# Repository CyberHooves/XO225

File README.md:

Haos Redro PN 0000 0003
Stereo 2.5-way electronic crossover
===================================

This is a stereo two way electronic crossover with mono subwoofer output. All inputs and outputs are balanced.

This was designed with fixed crossover frequencies and fixed gains for fixed applications. Applications wherein an adjustible crossover would have it's knobs maladjusted by knobs resulting in awful sound and burnt voice coils.

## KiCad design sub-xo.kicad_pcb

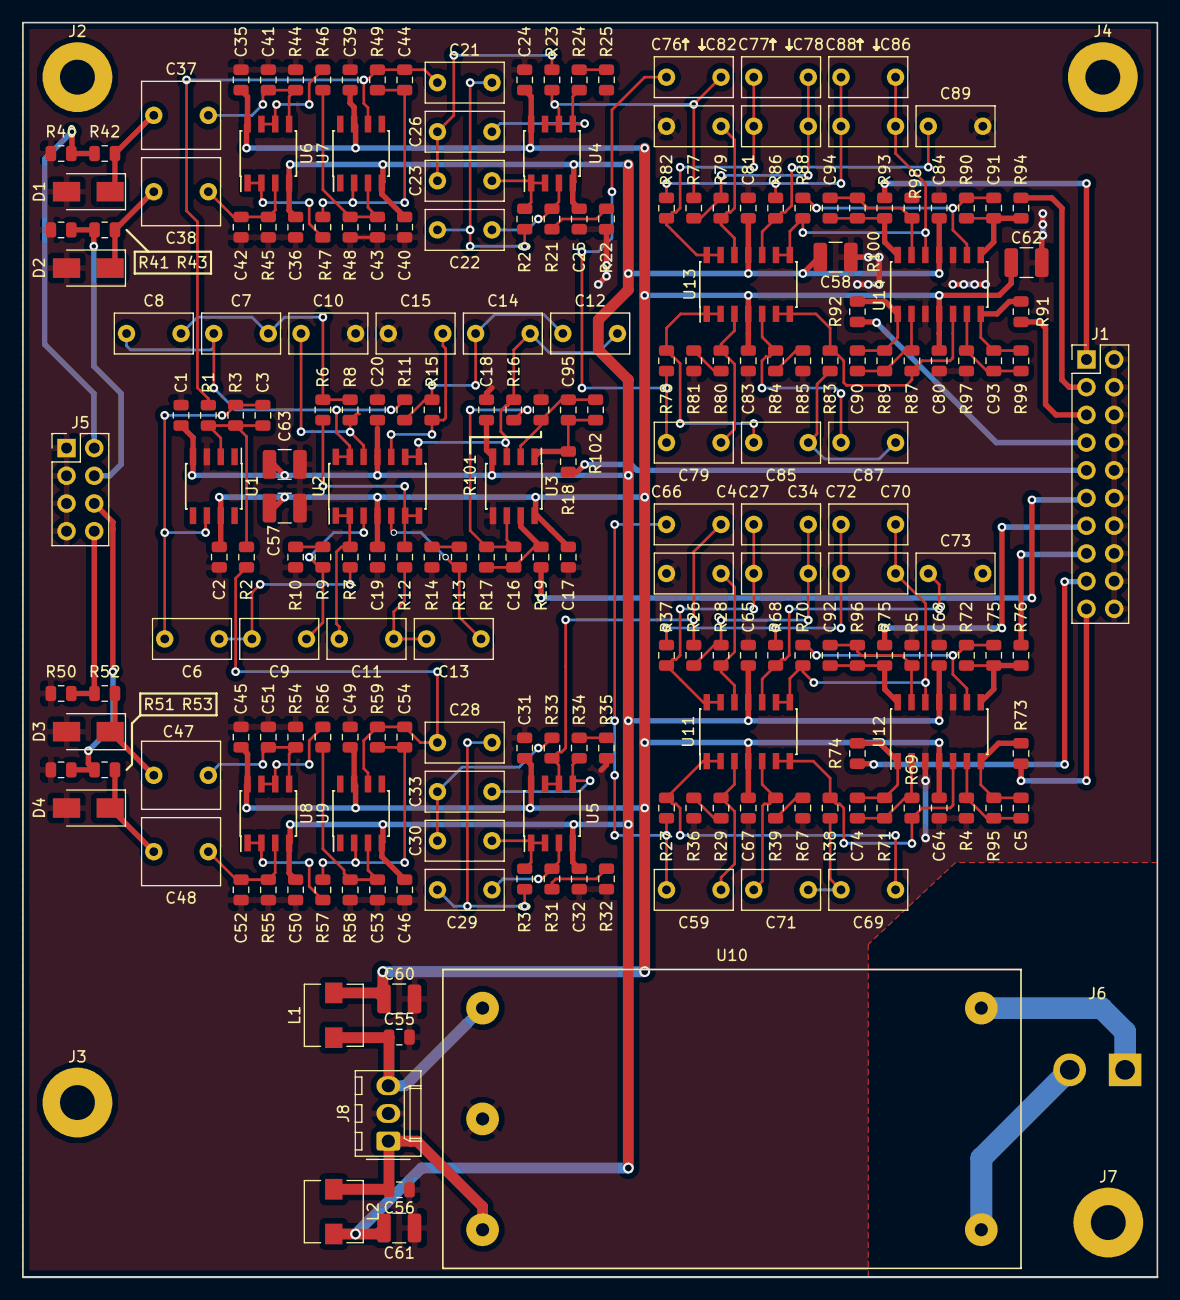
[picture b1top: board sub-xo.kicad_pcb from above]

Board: 2 copper layers, 104.0 x 115.0 mm, 218 parts (0 on the bottom side), 119 nets.

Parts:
C1, C2, C17, C18, C19, C20, C24, C25, C31, C32, C35, C36, C39, C40, C45, C46, C49, C50, C64, C65, C67, C68, C80, C81, C83, C84: 104; C_0805_2012Metric
C3, C5, C16, C43, C44, C53, C54, C74, C75, C90, C91, C92, C93, C94, C95: 151; C_0805_2012Metric
C4, C6, C9, C11, C13, C59, C69, C71, C76, C79, C85, C87: 334; C_Rect_L7.0mm_W3.5mm_P5.00mm
C7, C8, C10, C12, C14, C15, C21, C22, C23, C26, C27, C28, C29, C30, C33, C34, C66, C70, C72, C73, C77, C78, C82, C86, C88, C89: 224; C_Rect_L7.0mm_W3.5mm_P5.00mm
C37, C38, C47, C48: 105; C_Rect_L7.0mm_W6.0mm_P5.00mm
C41, C42, C51, C52: 101; C_0805_2012Metric
C55, C56: 105; C_0805_2012Metric
C57, C58, C60, C61, C62, C63: 335; C_1210_3225Metric
D1, D2, D3, D4: SMAJ7; D_SMA
J1: Conn_02x10_Odd_Even; PinHeader_2x10_P2.54mm_Vertical
J2, J3, J4, J7: Screwhole; MountingHole_3.2mm_M3_Pad
J5: Conn_02x04_Odd_Even; PinHeader_2x04_P2.54mm_Vertical
J6: Conn_01x02; CON-MOLEX-SPOX-5281-2P-V
J8: Conn_01x03; Molex_KK-254_AE-6410-03A_1x03_P2.54mm_Vertical
L1, L2: 22; L_Wuerth_HCI-5040
R1, R2, R3, R4, R5, R16, R42, R43, R46, R47, R48, R49, R52, R53, R56, R57, R58, R59, R69, R70, R72, R87, R88, R90, R97, R98, R101, R102: 10K; R_0805_2012Metric
R6, R8, R11, R15, R20, R21, R22, R23, R24, R25, R26, R28, R30, R31, R32, R33, R34, R35, R37, R68, R77, R79, R82, R86: 4K3; R_0805_2012Metric
R7, R9, R10, R12, R13, R14, R27, R29, R36, R38, R39, R67, R78, R80, R81, R83, R84, R85: 8K2; R_0805_2012Metric
R17, R71, R89, R95, R96, R99, R100: 20K; R_0805_2012Metric
R18, R19, R73, R74, R75, R76, R91, R92, R93, R94: 100; R_0805_2012Metric
R40, R41, R50, R51: 1M; R_0805_2012Metric
R44, R45, R54, R55: 220K; R_0805_2012Metric
U1, U7, U9: TL071; SOIC-8_3.9x4.9mm_P1.27mm
U2, U11, U12, U13, U14: TL074; SOIC-14_3.9x8.7mm_P1.27mm
U3, U4, U5, U6, U8: TL072; SOIC-8_3.9x4.9mm_P1.27mm
U10: RAC10-15DK277; RECOM-RAC10

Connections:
+15V: C2.2, C17.1, C19.1, C24.1, C31.1, C35.1, C39.1, C45.1, C49.1, C57.1, C60.1, C62.1, C64.1, C67.1, C80.1, C83.1, L1.2, U1.7, U2.4, U3.8, U4.8, U5.8, U6.8, U7.7, U8.8, U9.7, U11.4, U12.4, U13.4, U14.4
-15V: C1.1, C18.2, C20.2, C25.2, C32.2, C36.2, C40.2, C46.2, C50.2, C58.2, C61.2, C63.2, C65.2, C68.2, C81.2, C84.2, L2.2, U1.4, U2.11, U3.4, U4.4, U5.4, U6.4, U7.4, U8.4, U9.4, U11.11, U12.11, U13.11, U14.11
/CH1 XO/IN: C76.2, R23.1, R77.2, U4.6, U4.7
/CH1 highpass/IN: C21.2, C44.1, R1.2, R49.1, U7.6
/CH1_HI+: J1.5, R91.1
/CH1_HI-: J1.7, R92.1
/CH1_IN+: J5.2, R40.1, R42.2
/CH1_IN-: J5.4, R41.1, R43.2
/CH1_LO+: J1.1, R93.1
/CH1_LO-: J1.3, R94.1
/CH2 XO/IN: C4.2, R26.2, R33.1, U5.6, U5.7
/CH2 highpass/IN: C28.2, C54.1, R2.2, R59.1, U9.6
/CH2_HI+: J1.19, R73.1
/CH2_HI-: J1.17, R74.1
/CH2_IN+: J5.8, R50.1, R52.2
/CH2_IN-: J5.6, R51.1, R53.2
/CH2_LO+: J1.13, R75.1
/CH2_LO-: J1.15, R76.1
/SUB_OUT+: J1.9, R18.1
/SUB_OUT-: J1.11, R19.1
/Sub XO/IN: C3.1, C6.2, R3.1, U1.6
GNDA: C1.2, C2.1, C10.2, C15.2, C17.2, C18.1, C19.2, C20.1, C24.2, C25.1, C31.2, C32.1, C35.2, C36.1, C39.2, C40.1, C41.2, C42.2, C43.1, C45.2, C46.1, C49.2, C50.1, C51.2, C52.2, C53.1, C55.2, C56.1, C57.2, C58.1, C60.2, C61.1, C62.2, C63.1, C64.2, C65.1, C66.2, C67.2, C68.1, C73.2, C80.2, C81.1, C82.2, C83.2, C84.1, C89.2, D1.2, D2.2, D3.2, D4.2, J1.2, J1.4, J1.6, J1.8, J1.10, J1.12, J1.14, J1.16, J1.18, J1.20, J5.1, J5.3, J5.5, J5.7, J8.2, R4.2, R5.2, R10.2, R14.2, R22.2, R25.2, R32.2, R35.2, R36.2, R40.2, R41.2, R44.2, R45.2, R48.1, R50.2, R51.2, R54.2, R55.2, R58.1, R67.2, R81.2, R85.2, R97.2, R98.2, R101.2, U1.3, U3.5, U10.4, U12.3, U12.10, U14.3, U14.10
unnamed: C3.2, R1.1, R2.1, R3.2, U1.2
unnamed: C4.1, C59.2, R27.2
unnamed: C5.1, R73.2, R95.1, U12.7
unnamed: C5.2, R4.1, R95.2, U12.6
unnamed: C6.1, C9.2, R7.2
unnamed: C7.1, C8.1, R11.2, U2.13, U2.14
unnamed: C7.2, C8.2, R6.1, R8.2
unnamed: C9.1, R9.1, U2.3
unnamed: C10.1, R8.1, U2.12
unnamed: C11.1, C13.2, R12.2
unnamed: C11.2, R7.1, U2.1, U2.2
unnamed: C12.1, C14.1, R16.2, U2.8, U2.9, U3.3
unnamed: C12.2, C14.2, R11.1, R15.2
unnamed: C13.1, R13.1, U2.5
unnamed: C15.1, R15.1, U2.10
unnamed: C16.1, R17.1, R19.2, U3.7
unnamed: C16.2, R16.1, R17.2, U3.6
unnamed: C21.1, C22.2, R20.2
unnamed: C22.1, R21.1, U4.3
unnamed: C23.1, C26.2, R23.2
unnamed: C23.2, R20.1, U4.1, U4.2
unnamed: C26.1, R24.1, U4.5
unnamed: C27.1, C34.1, R37.2, U11.13, U11.14
unnamed: C27.2, C34.2, R26.1, R28.2
unnamed: C28.1, C29.2, R30.2
unnamed: C29.1, R31.1, U5.3
unnamed: C30.1, C33.2, R33.2
unnamed: C30.2, R30.1, U5.1, U5.2
unnamed: C33.1, R34.1, U5.5
unnamed: C37.1, C41.1, R44.1, U6.5
unnamed: C37.2, D1.1, R42.1
unnamed: C38.1, C42.1, R45.1, U6.3
unnamed: C38.2, D2.1, R43.1
unnamed: C43.2, R46.1, R48.2, U7.3
unnamed: C44.2, R47.1, R49.2, U7.2
unnamed: C47.1, C51.1, R54.1, U8.5
unnamed: C47.2, D3.1, R52.1
unnamed: C48.1, C52.1, R55.1, U8.3
unnamed: C48.2, D4.1, R53.1
unnamed: C53.2, R56.1, R58.2, U9.3
unnamed: C54.2, R57.1, R59.2, U9.2
unnamed: C55.1, J8.3, L1.1, U10.3
unnamed: C56.2, J8.1, L2.1, U10.5
unnamed: C59.1, R29.1, U11.3
unnamed: C66.1, R28.1, U11.12
unnamed: C69.1, C71.2, R38.2
unnamed: C69.2, R27.1, U11.1, U11.2
unnamed: C70.1, C72.1, R70.2, U11.8, U11.9, U12.12
unnamed: C70.2, C72.2, R37.1, R68.2
unnamed: C71.1, R39.1, U11.5
unnamed: C73.1, R68.1, U11.10
unnamed: C74.1, R71.1, R74.2, U12.1
unnamed: C74.2, R69.1, R71.2, U12.2
unnamed: C75.1, R72.1, R76.2, U12.8
unnamed: C75.2, R70.1, R72.2, U12.9
unnamed: C76.1, C79.2, R78.2
unnamed: C77.1, C78.1, R82.2, U13.13, U13.14
unnamed: C77.2, C78.2, R77.1, R79.2
unnamed: C79.1, R80.1, U13.3
unnamed: C82.1, R79.1, U13.12
unnamed: C85.1, C87.2, R83.2
unnamed: C85.2, R78.1, U13.1, U13.2
unnamed: C86.1, C88.1, R88.2, U13.8, U13.9, U14.12
unnamed: C86.2, C88.2, R82.1, R86.2
unnamed: C87.1, R84.1, U13.5
unnamed: C89.1, R86.1, U13.10
unnamed: C90.1, R89.1, R92.2, U14.1
unnamed: C90.2, R87.1, R89.2, U14.2
unnamed: C91.1, R90.1, R94.2, U14.8
unnamed: C91.2, R88.1, R90.2, U14.9
unnamed: C92.1, R75.2, R96.1, U12.14
unnamed: C92.2, R5.1, R96.2, U12.13
unnamed: C93.1, R91.2, R99.1, U14.7
unnamed: C93.2, R97.1, R99.2, U14.6
unnamed: C94.1, R93.2, R100.1, U14.14
unnamed: C94.2, R98.1, R100.2, U14.13
unnamed: C95.1, R18.2, R102.1, U3.1
unnamed: C95.2, R101.1, R102.2, U3.2
unnamed: J6.1, U10.1
unnamed: J6.2, U10.2
unnamed: R9.2, R10.1
unnamed: R6.2, R12.1, U2.6, U2.7
unnamed: R13.2, R14.1
unnamed: R21.2, R22.1
unnamed: R24.2, R25.1
unnamed: R29.2, R36.1
unnamed: R31.2, R32.1
unnamed: R34.2, R35.1
unnamed: R38.1, R69.2, U11.6, U11.7, U12.5
unnamed: R39.2, R67.1
unnamed: R46.2, U6.6, U6.7
unnamed: R47.2, U6.1, U6.2
unnamed: R56.2, U8.6, U8.7
unnamed: R57.2, U8.1, U8.2
unnamed: R80.2, R81.1
unnamed: R83.1, R87.2, U13.6, U13.7, U14.5
unnamed: R84.2, R85.1
